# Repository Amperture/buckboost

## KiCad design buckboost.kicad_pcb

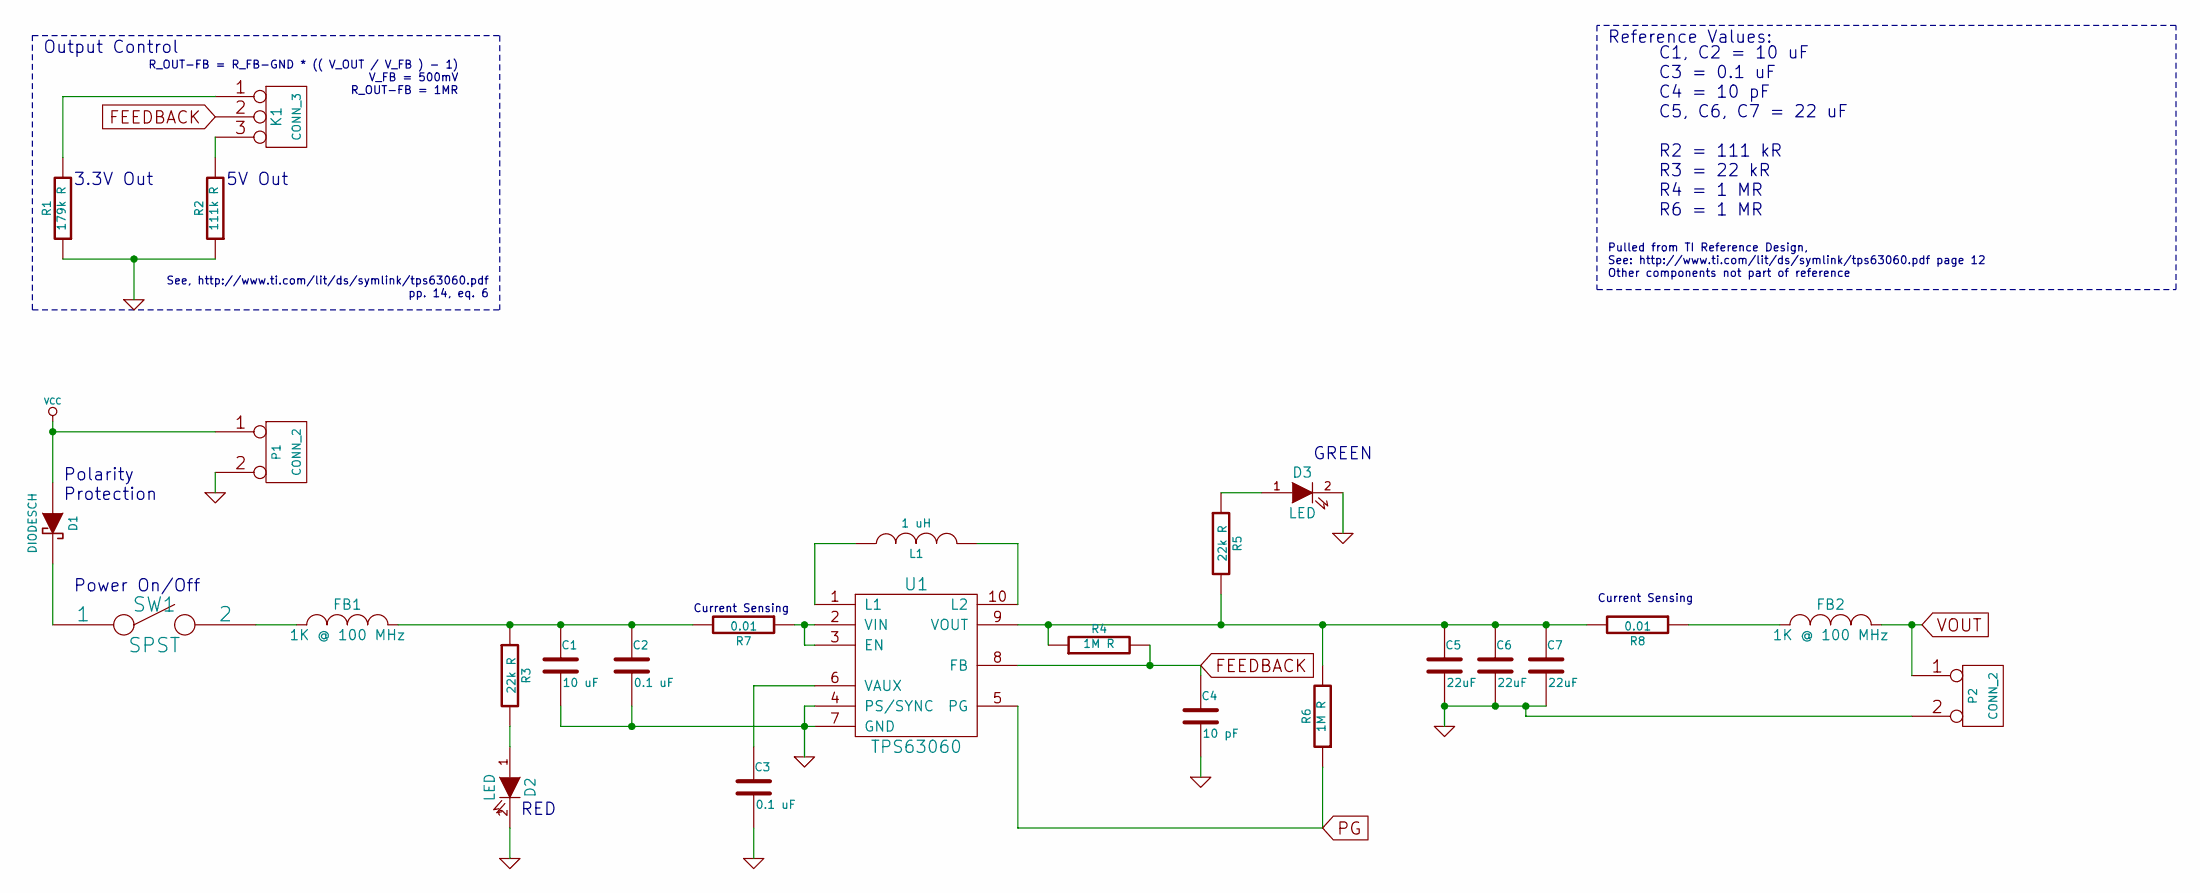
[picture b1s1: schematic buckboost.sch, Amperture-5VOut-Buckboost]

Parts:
C1: 10 uF; C_0805_HandSoldering
C2, C3: 0.1 uF; C_0805_HandSoldering
C4: 10 pF; C_0805_HandSoldering
C5, C6, C7: 22uF; C_0805_HandSoldering
D1: DIODESCH; C_1206_HandSoldering
D2, D3: LED; LED_0805
FB1, FB2: 1K @ 100 MHz; C_1210_HandSoldering
K1: CONN_3; Pin_Header_Straight_1x03
L1: 1 uH; XFL4020
P1, P2: CONN_2; Pin_Header_Straight_1x02
R1: 179k R; R_0805_HandSoldering
R2: 111k R; R_0805_HandSoldering
R3, R5: 22k R; R_0805_HandSoldering
R4, R6: 1M R; R_0805_HandSoldering
R7, R8: 0.01; R_0805_HandSoldering
SW1: SPST; SW_DIP_x1_Slide
U1: TPS63060; DFN-10-1EP_3x3mm_Pitch0.5mm

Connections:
FEEDBACK: C4.1, K1.2 (PM), R4.2, U1.8 (FB)
GND: C1.2, C2.2, C3.2, C4.2, C5.2, C6.2, C7.2, D2.2 (K), D3.2 (K), P1.2 (PM), P2.2 (PM), R1.1, R2.1, U1.4 (PS/SYNC), U1.7 (GND)
unnamed: C1.1, C2.1, FB1.2, R3.1, R7.2
unnamed: C3.1, U1.6 (VAUX)
unnamed: C5.1, C6.1, C7.1, R4.1, R5.2, R6.2, R8.2, U1.9 (VOUT)
unnamed: D1.2 (K), SW1.1
unnamed: D2.1 (A), R3.2
unnamed: D3.1 (A), R5.1
unnamed: FB1.1, SW1.2
unnamed: FB2.1, R8.1
unnamed: K1.1, R1.2
unnamed: K1.3, R2.2
unnamed: L1.1, U1.1 (L1)
unnamed: L1.2, U1.10 (L2)
unnamed: R7.1, U1.2 (VIN), U1.3 (EN)
PG: R6.1, U1.5 (PG)
VCC: D1.1 (A), P1.1
VOUT: FB2.2, P2.1

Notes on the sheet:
Polarity Protection
Power On/Off
RED
GREEN
Reference Values:
5V Out
3.3V Out
Output Control
R_OUT-FB = R_FB-GND * (( V_OUT / V_FB ) - 1) V_FB = 500mV R_OUT-FB = 1MR
See, http://www.ti.com/lit/ds/symlink/tps63060.pdf pp. 14, eq. 6
Pulled from TI Reference Design, See: http://www.ti.com/lit/ds/symlink/tps63060.pdf page 12 Other components not part of reference
C1, C2 = 10 uF C3 = 0.1 uF C4 = 10 pF C5, C6, C7 = 22 uF R2 = 111 kR R3 = 22 kR R4 = 1 MR R6 = 1 MR
Current Sensing

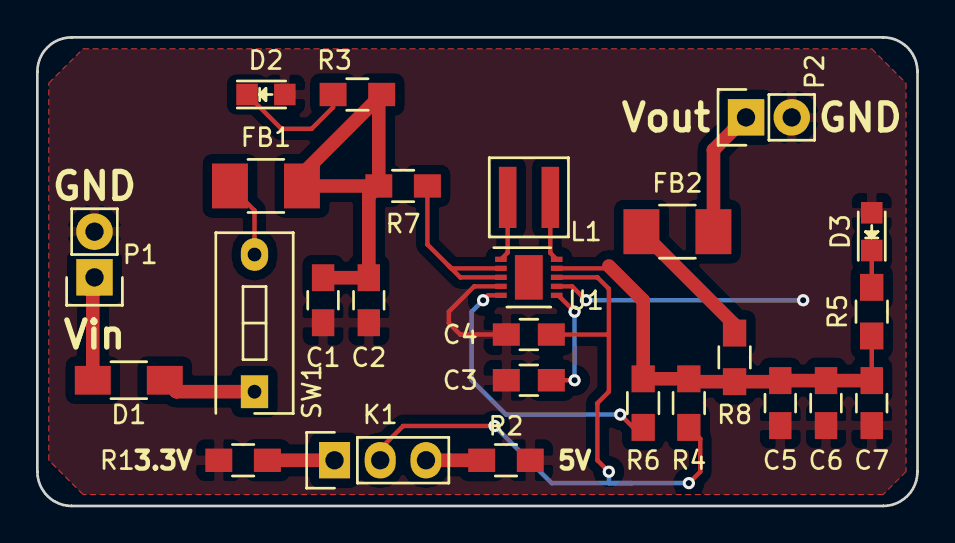
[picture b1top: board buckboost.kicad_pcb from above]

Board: 2 copper layers, 48.9 x 26.0 mm, 26 parts (0 on the bottom side), 18 nets.

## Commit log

2016-03-20 Early current state, TPS63060 part with recommended design, added on/off switch and protection schottkey.
2016-03-20 Added current state preview pdf.
2016-03-21 Added output control via 0.1" Header.
2016-03-21 Removed redundant feedback resistor.
2016-03-21 Added reference value chart from TI datasheet.
2016-03-23 Schematic Largely Done, many footprints chosen, footprint for Inductor custom made.
2016-03-23 Added preview for XFL4020 Coilcraft footprint.
2016-03-23 Updated schematic preview to latest version of schematic.
2016-04-07 Footprints chosen, PCB starting. No preview.
2016-04-07 Board Rev1 Done.
2016-04-07 Revision 1
2016-04-07 Fixing tracks for OSHPark design rules.
2016-04-08 Housecleaning
2016-04-08 Preview of schematic
